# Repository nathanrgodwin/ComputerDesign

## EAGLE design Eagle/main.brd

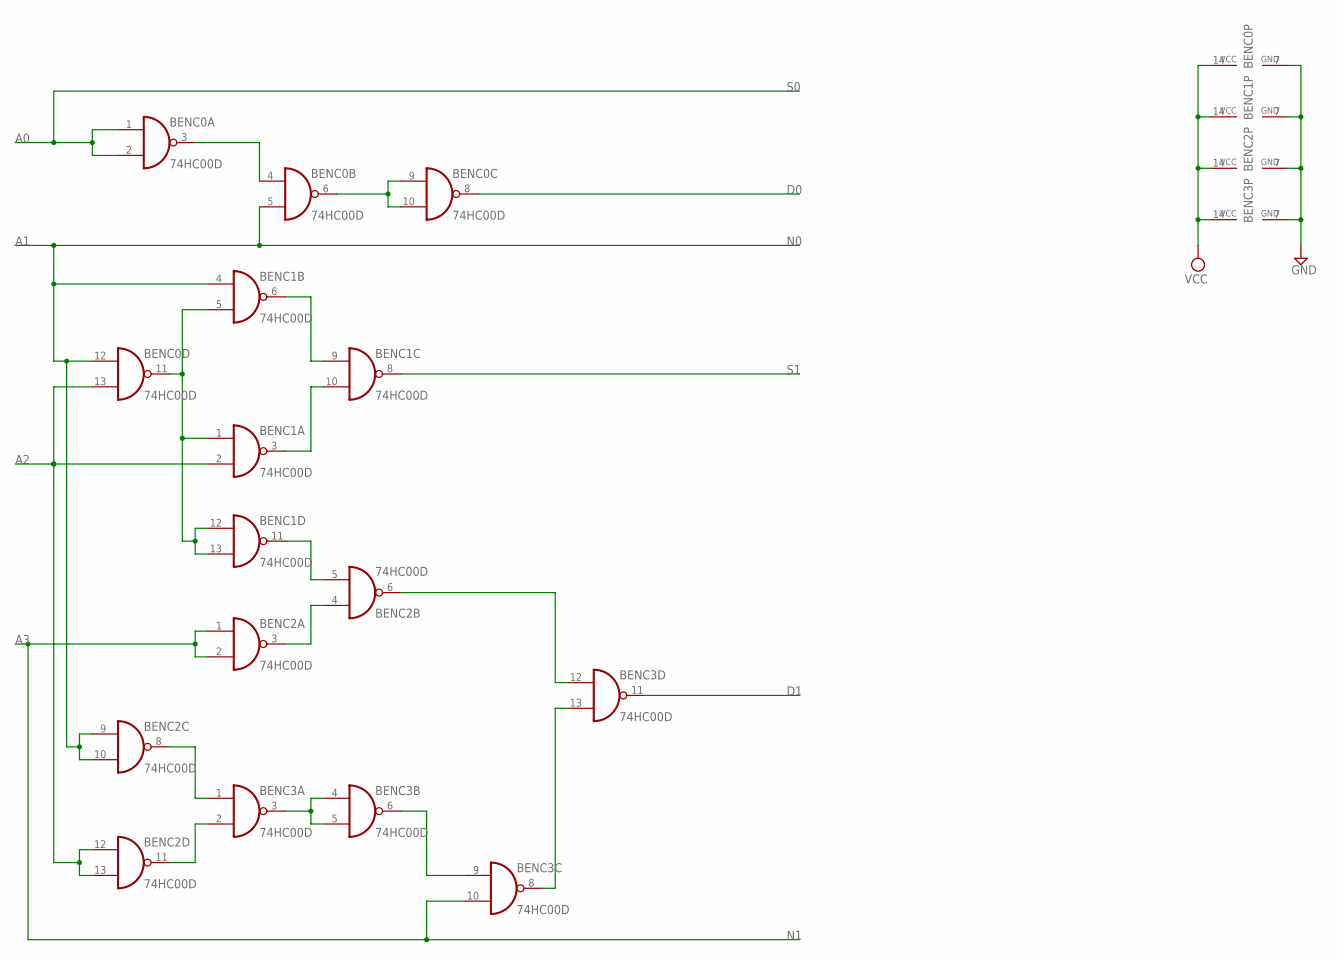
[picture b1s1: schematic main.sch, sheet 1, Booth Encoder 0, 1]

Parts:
BENC0, BENC1, BENC2, BENC3: 74HC00D; SO14

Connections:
A0: BENC0.1 (I0), BENC0.2 (I1); also elsewhere on the board
A1: BENC0.5 (I1), BENC0.12 (I0), BENC1.4 (I0), BENC2.9 (I0), BENC2.10 (I1); also elsewhere on the board
A2: BENC0.13 (I1), BENC1.2 (I1), BENC2.12 (I0), BENC2.13 (I1); also elsewhere on the board
A3: BENC2.1 (I0), BENC2.2 (I1), BENC3.10 (I1); also elsewhere on the board
D0: BENC0.8 (O); also elsewhere on the board
D1: BENC3.11 (O); also elsewhere on the board
GND: BENC0.7 (GND), BENC1.7 (GND), BENC2.7 (GND), BENC3.7 (GND); also elsewhere on the board
unnamed: BENC0.3 (O), BENC0.4 (I0)
unnamed: BENC0.6 (O), BENC0.9 (I0), BENC0.10 (I1)
unnamed: BENC2.6 (O), BENC3.12 (I0)
unnamed: BENC1.3 (O), BENC1.10 (I1)
unnamed: BENC1.6 (O), BENC1.9 (I0)
unnamed: BENC3.8 (O), BENC3.13 (I1)
unnamed: BENC2.3 (O), BENC2.4 (I0)
unnamed: BENC1.11 (O), BENC2.5 (I1)
unnamed: BENC2.11 (O), BENC3.2 (I1)
unnamed: BENC2.8 (O), BENC3.1 (I0)
unnamed: BENC3.3 (O), BENC3.4 (I0), BENC3.5 (I1)
unnamed: BENC3.6 (O), BENC3.9 (I0)
unnamed: BENC0.11 (O), BENC1.1 (I0), BENC1.5 (I1), BENC1.12 (I0), BENC1.13 (I1)
S1: BENC1.8 (O); also elsewhere on the board
VCC: BENC0.14 (VCC), BENC1.14 (VCC), BENC2.14 (VCC), BENC3.14 (VCC); also elsewhere on the board

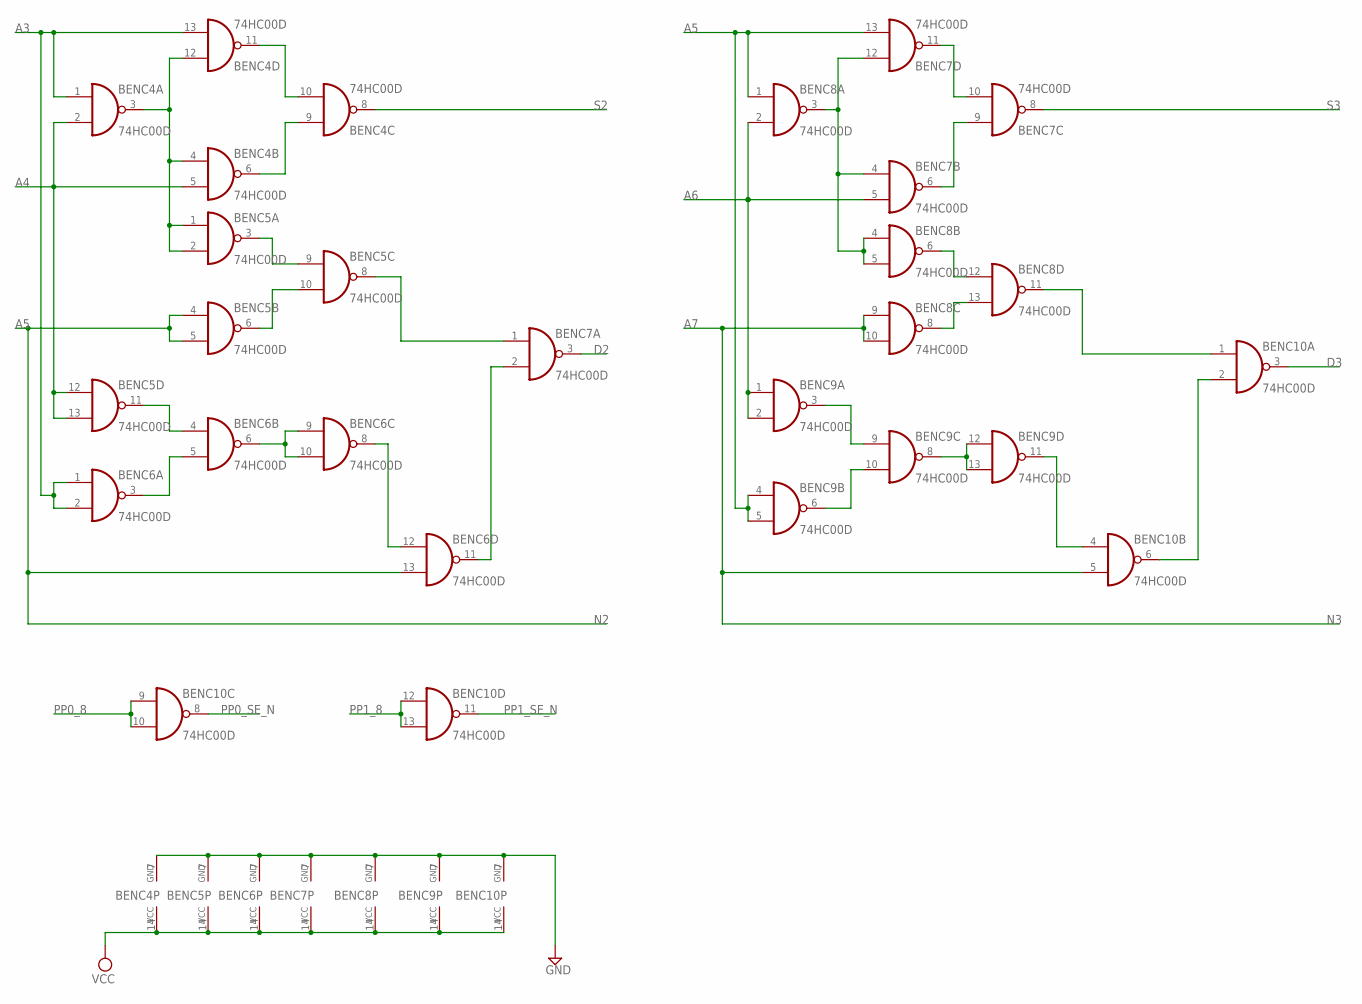
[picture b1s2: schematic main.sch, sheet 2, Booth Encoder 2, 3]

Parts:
BENC4, BENC5, BENC6, BENC7, BENC8, BENC9, BENC10: 74HC00D; SO14

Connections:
A3: BENC4.1 (I0), BENC4.13 (I1), BENC6.1 (I0), BENC6.2 (I1); also elsewhere on the board
A4: BENC4.2 (I1), BENC4.5 (I1), BENC5.12 (I0), BENC5.13 (I1); also elsewhere on the board
A5: BENC5.4 (I0), BENC5.5 (I1), BENC6.13 (I1), BENC7.13 (I1), BENC8.1 (I0), BENC9.4 (I0), BENC9.5 (I1); also elsewhere on the board
A6: BENC7.5 (I1), BENC8.2 (I1), BENC9.1 (I0), BENC9.2 (I1); also elsewhere on the board
A7: BENC8.9 (I0), BENC8.10 (I1), BENC10.5 (I1); also elsewhere on the board
D2: BENC7.3 (O); also elsewhere on the board
D3: BENC10.3 (O); also elsewhere on the board
GND: BENC4.7 (GND), BENC5.7 (GND), BENC6.7 (GND), BENC7.7 (GND), BENC8.7 (GND), BENC9.7 (GND), BENC10.7 (GND); also elsewhere on the board
unnamed: BENC4.3 (O), BENC4.4 (I0), BENC4.12 (I0), BENC5.1 (I0), BENC5.2 (I1)
unnamed: BENC4.6 (O), BENC4.9 (I0)
unnamed: BENC4.10 (I1), BENC4.11 (O)
unnamed: BENC6.11 (O), BENC7.2 (I1)
unnamed: BENC5.3 (O), BENC5.9 (I0)
unnamed: BENC5.6 (O), BENC5.10 (I1)
unnamed: BENC5.8 (O), BENC7.1 (I0)
unnamed: BENC6.6 (O), BENC6.9 (I0), BENC6.10 (I1)
unnamed: BENC6.8 (O), BENC6.12 (I0)
unnamed: BENC5.11 (O), BENC6.4 (I0)
unnamed: BENC6.3 (O), BENC6.5 (I1)
unnamed: BENC7.10 (I1), BENC7.11 (O)
unnamed: BENC7.6 (O), BENC7.9 (I0)
unnamed: BENC7.4 (I0), BENC7.12 (I0), BENC8.3 (O), BENC8.4 (I0), BENC8.5 (I1)
unnamed: BENC8.8 (O), BENC8.13 (I1)
unnamed: BENC8.6 (O), BENC8.12 (I0)
unnamed: BENC8.11 (O), BENC10.1 (I0)
unnamed: BENC10.2 (I1), BENC10.6 (O)
unnamed: BENC9.11 (O), BENC10.4 (I0)
unnamed: BENC9.8 (O), BENC9.12 (I0), BENC9.13 (I1)
unnamed: BENC9.6 (O), BENC9.10 (I1)
unnamed: BENC9.3 (O), BENC9.9 (I0)
PP0_8: BENC10.9 (I0), BENC10.10 (I1); also elsewhere on the board
PP0_SE_N: BENC10.8 (O); also elsewhere on the board
PP1_8: BENC10.12 (I0), BENC10.13 (I1); also elsewhere on the board
PP1_SE_N: BENC10.11 (O); also elsewhere on the board
S2: BENC4.8 (O); also elsewhere on the board
S3: BENC7.8 (O); also elsewhere on the board
VCC: BENC4.14 (VCC), BENC5.14 (VCC), BENC6.14 (VCC), BENC7.14 (VCC), BENC8.14 (VCC), BENC9.14 (VCC), BENC10.14 (VCC); also elsewhere on the board

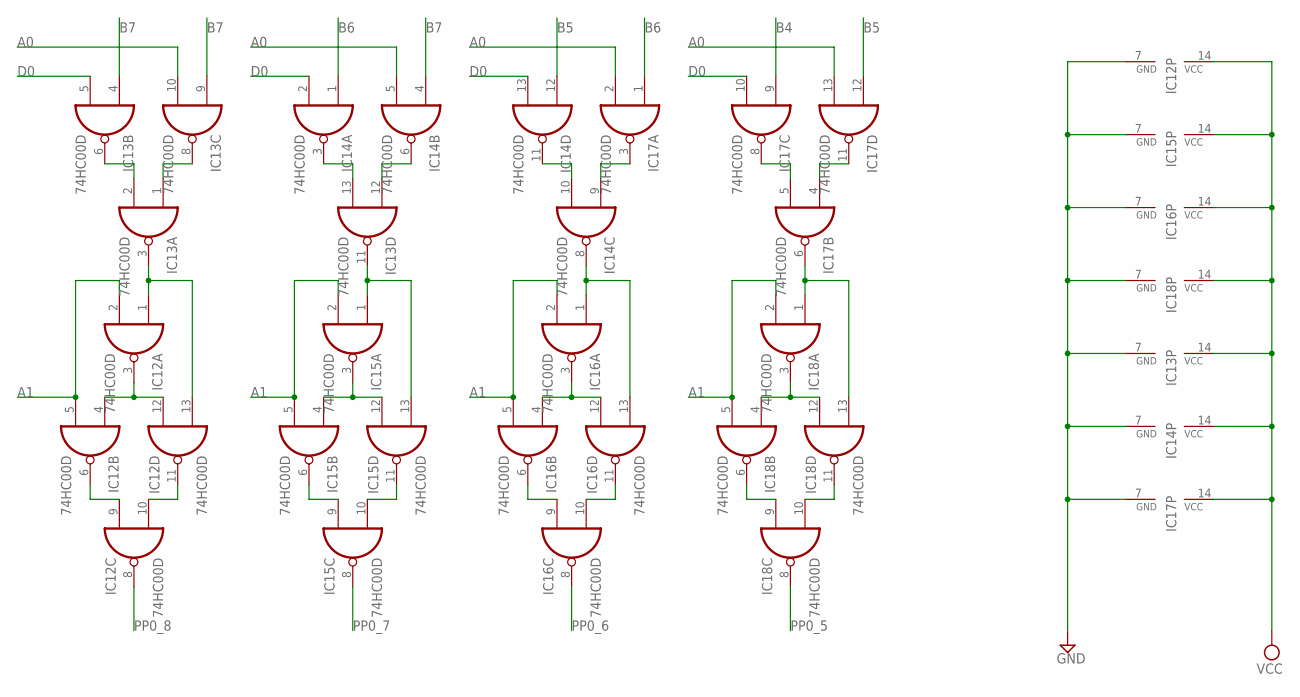
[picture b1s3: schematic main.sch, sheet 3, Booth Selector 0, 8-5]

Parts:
IC12, IC13, IC14, IC15, IC16, IC17, IC18: 74HC00D; SO14

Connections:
A0: IC13.10 (I1), IC14.5 (I1), IC17.2 (I1), IC17.13 (I1); also elsewhere on the board
A1: IC12.2 (I1), IC12.5 (I1), IC15.2 (I1), IC15.5 (I1), IC16.2 (I1), IC16.5 (I1), IC18.2 (I1), IC18.5 (I1); also elsewhere on the board
B4: IC17.9 (I0); also elsewhere on the board
B5: IC14.12 (I0), IC17.12 (I0); also elsewhere on the board
B6: IC14.1 (I0), IC17.1 (I0); also elsewhere on the board
B7: IC13.4 (I0), IC13.9 (I0), IC14.4 (I0); also elsewhere on the board
D0: IC13.5 (I1), IC14.2 (I1), IC14.13 (I1), IC17.10 (I1); also elsewhere on the board
GND: IC12.7 (GND), IC13.7 (GND), IC14.7 (GND), IC15.7 (GND), IC16.7 (GND), IC17.7 (GND), IC18.7 (GND); also elsewhere on the board
unnamed: IC12.6 (O), IC12.9 (I0)
unnamed: IC12.10 (I1), IC12.11 (O)
unnamed: IC12.3 (O), IC12.4 (I0), IC12.12 (I0)
unnamed: IC15.6 (O), IC15.9 (I0)
unnamed: IC15.10 (I1), IC15.11 (O)
unnamed: IC15.3 (O), IC15.4 (I0), IC15.12 (I0)
unnamed: IC16.3 (O), IC16.4 (I0), IC16.12 (I0)
unnamed: IC16.10 (I1), IC16.11 (O)
unnamed: IC16.6 (O), IC16.9 (I0)
unnamed: IC13.11 (O), IC15.1 (I0), IC15.13 (I1)
unnamed: IC13.13 (I1), IC14.3 (O)
unnamed: IC13.12 (I0), IC14.6 (O)
unnamed: IC13.1 (I0), IC13.8 (O)
unnamed: IC13.2 (I1), IC13.6 (O)
unnamed: IC14.10 (I1), IC14.11 (O)
unnamed: IC14.9 (I0), IC17.3 (O)
unnamed: IC17.5 (I1), IC17.8 (O)
unnamed: IC17.4 (I0), IC17.11 (O)
unnamed: IC17.6 (O), IC18.1 (I0), IC18.13 (I1)
unnamed: IC14.8 (O), IC16.1 (I0), IC16.13 (I1)
unnamed: IC12.1 (I0), IC12.13 (I1), IC13.3 (O)
unnamed: IC18.3 (O), IC18.4 (I0), IC18.12 (I0)
unnamed: IC18.6 (O), IC18.9 (I0)
unnamed: IC18.10 (I1), IC18.11 (O)
PP0_5: IC18.8 (O); also elsewhere on the board
PP0_6: IC16.8 (O); also elsewhere on the board
PP0_7: IC15.8 (O); also elsewhere on the board
PP0_8: IC12.8 (O); also elsewhere on the board
VCC: IC12.14 (VCC), IC13.14 (VCC), IC14.14 (VCC), IC15.14 (VCC), IC16.14 (VCC), IC17.14 (VCC), IC18.14 (VCC); also elsewhere on the board

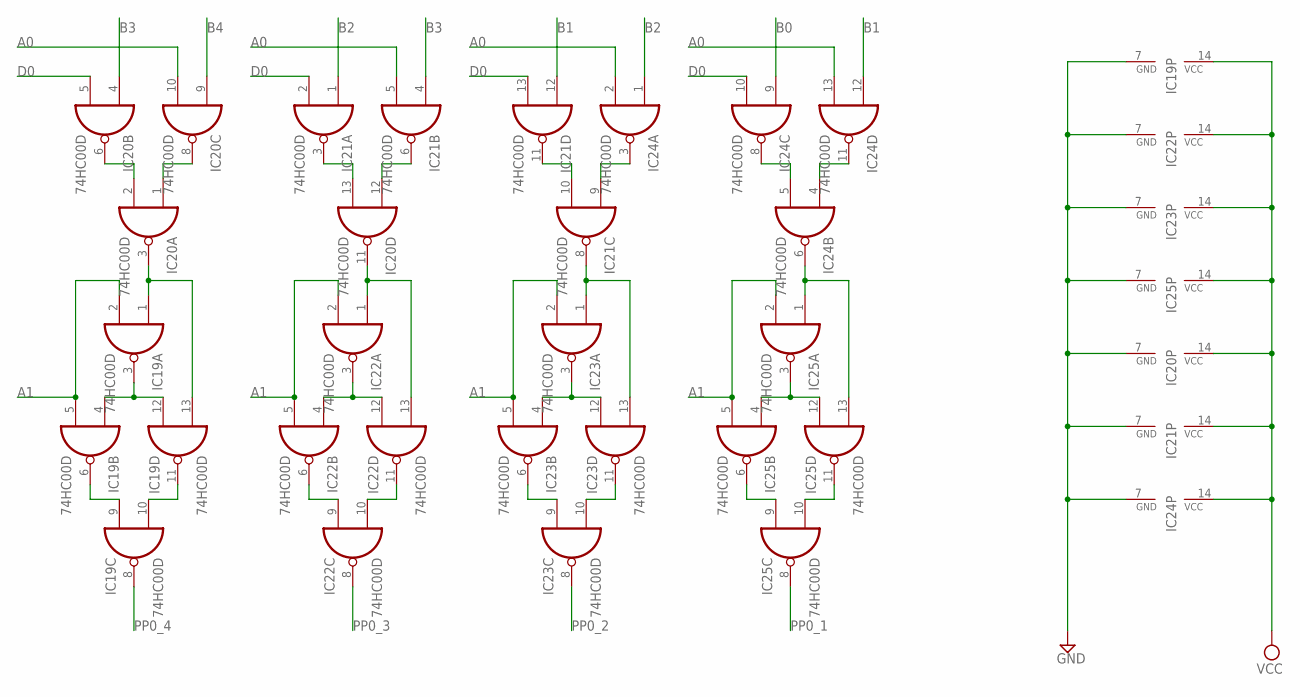
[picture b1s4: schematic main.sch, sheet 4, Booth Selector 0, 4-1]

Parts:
IC19, IC20, IC21, IC22, IC23, IC24, IC25: 74HC00D; SO14

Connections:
A0: IC20.10 (I1), IC21.5 (I1), IC24.2 (I1), IC24.13 (I1); also elsewhere on the board
A1: IC19.2 (I1), IC19.5 (I1), IC22.2 (I1), IC22.5 (I1), IC23.2 (I1), IC23.5 (I1), IC25.2 (I1), IC25.5 (I1); also elsewhere on the board
B0: IC24.9 (I0); also elsewhere on the board
B1: IC21.12 (I0), IC24.12 (I0); also elsewhere on the board
B2: IC21.1 (I0), IC24.1 (I0); also elsewhere on the board
B3: IC20.4 (I0), IC21.4 (I0); also elsewhere on the board
B4: IC20.9 (I0); also elsewhere on the board
D0: IC20.5 (I1), IC21.2 (I1), IC21.13 (I1), IC24.10 (I1); also elsewhere on the board
GND: IC19.7 (GND), IC20.7 (GND), IC21.7 (GND), IC22.7 (GND), IC23.7 (GND), IC24.7 (GND), IC25.7 (GND); also elsewhere on the board
unnamed: IC19.6 (O), IC19.9 (I0)
unnamed: IC19.10 (I1), IC19.11 (O)
unnamed: IC19.3 (O), IC19.4 (I0), IC19.12 (I0)
unnamed: IC22.6 (O), IC22.9 (I0)
unnamed: IC22.10 (I1), IC22.11 (O)
unnamed: IC22.3 (O), IC22.4 (I0), IC22.12 (I0)
unnamed: IC23.3 (O), IC23.4 (I0), IC23.12 (I0)
unnamed: IC23.10 (I1), IC23.11 (O)
unnamed: IC23.6 (O), IC23.9 (I0)
unnamed: IC20.11 (O), IC22.1 (I0), IC22.13 (I1)
unnamed: IC20.13 (I1), IC21.3 (O)
unnamed: IC20.12 (I0), IC21.6 (O)
unnamed: IC20.1 (I0), IC20.8 (O)
unnamed: IC20.2 (I1), IC20.6 (O)
unnamed: IC21.10 (I1), IC21.11 (O)
unnamed: IC21.9 (I0), IC24.3 (O)
unnamed: IC24.5 (I1), IC24.8 (O)
unnamed: IC24.4 (I0), IC24.11 (O)
unnamed: IC24.6 (O), IC25.1 (I0), IC25.13 (I1)
unnamed: IC21.8 (O), IC23.1 (I0), IC23.13 (I1)
unnamed: IC19.1 (I0), IC19.13 (I1), IC20.3 (O)
unnamed: IC25.3 (O), IC25.4 (I0), IC25.12 (I0)
unnamed: IC25.6 (O), IC25.9 (I0)
unnamed: IC25.10 (I1), IC25.11 (O)
PP0_1: IC25.8 (O); also elsewhere on the board
PP0_2: IC23.8 (O); also elsewhere on the board
PP0_3: IC22.8 (O); also elsewhere on the board
PP0_4: IC19.8 (O); also elsewhere on the board
VCC: IC19.14 (VCC), IC20.14 (VCC), IC21.14 (VCC), IC22.14 (VCC), IC23.14 (VCC), IC24.14 (VCC), IC25.14 (VCC); also elsewhere on the board

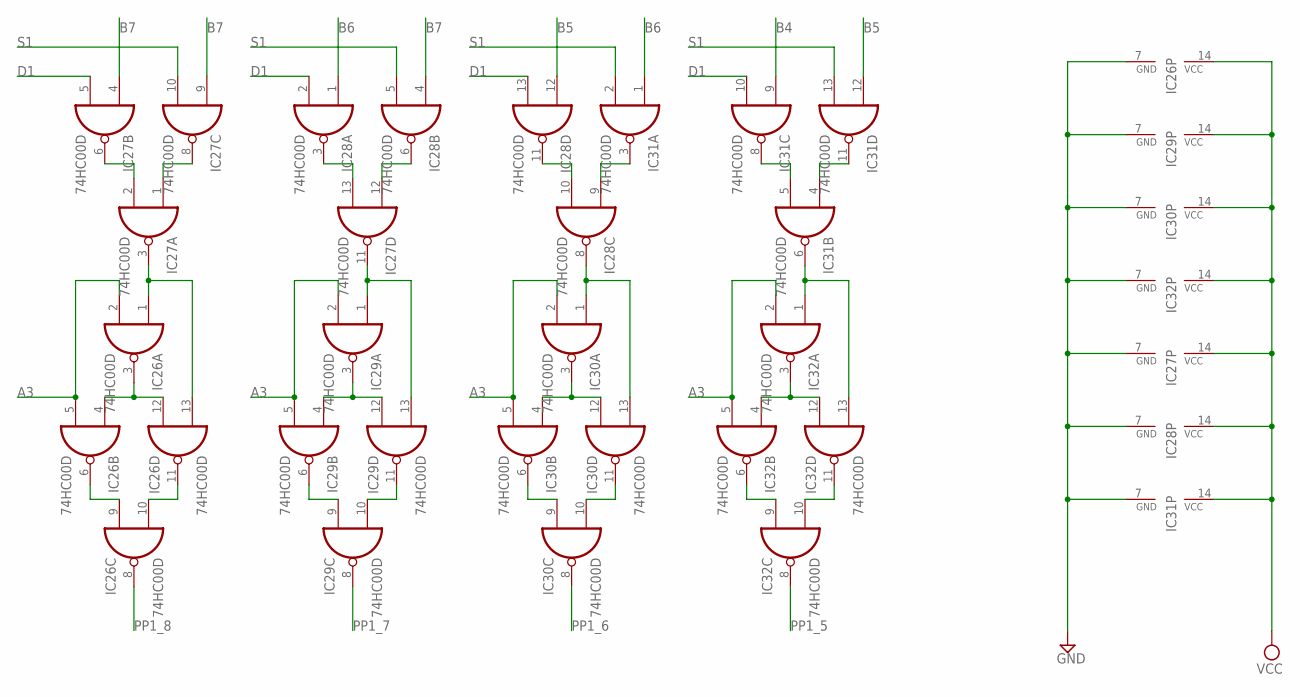
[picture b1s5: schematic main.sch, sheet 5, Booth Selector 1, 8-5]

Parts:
IC26, IC27, IC28, IC29, IC30, IC31, IC32: 74HC00D; SO14

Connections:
A3: IC26.2 (I1), IC26.5 (I1), IC29.2 (I1), IC29.5 (I1), IC30.2 (I1), IC30.5 (I1), IC32.2 (I1), IC32.5 (I1); also elsewhere on the board
B4: IC31.9 (I0); also elsewhere on the board
B5: IC28.12 (I0), IC31.12 (I0); also elsewhere on the board
B6: IC28.1 (I0), IC31.1 (I0); also elsewhere on the board
B7: IC27.4 (I0), IC27.9 (I0), IC28.4 (I0); also elsewhere on the board
D1: IC27.5 (I1), IC28.2 (I1), IC28.13 (I1), IC31.10 (I1); also elsewhere on the board
GND: IC26.7 (GND), IC27.7 (GND), IC28.7 (GND), IC29.7 (GND), IC30.7 (GND), IC31.7 (GND), IC32.7 (GND); also elsewhere on the board
unnamed: IC26.6 (O), IC26.9 (I0)
unnamed: IC26.10 (I1), IC26.11 (O)
unnamed: IC26.3 (O), IC26.4 (I0), IC26.12 (I0)
unnamed: IC29.6 (O), IC29.9 (I0)
unnamed: IC29.10 (I1), IC29.11 (O)
unnamed: IC29.3 (O), IC29.4 (I0), IC29.12 (I0)
unnamed: IC30.3 (O), IC30.4 (I0), IC30.12 (I0)
unnamed: IC30.10 (I1), IC30.11 (O)
unnamed: IC30.6 (O), IC30.9 (I0)
unnamed: IC27.11 (O), IC29.1 (I0), IC29.13 (I1)
unnamed: IC27.13 (I1), IC28.3 (O)
unnamed: IC27.12 (I0), IC28.6 (O)
unnamed: IC27.1 (I0), IC27.8 (O)
unnamed: IC27.2 (I1), IC27.6 (O)
unnamed: IC28.10 (I1), IC28.11 (O)
unnamed: IC28.9 (I0), IC31.3 (O)
unnamed: IC31.5 (I1), IC31.8 (O)
unnamed: IC31.4 (I0), IC31.11 (O)
unnamed: IC31.6 (O), IC32.1 (I0), IC32.13 (I1)
unnamed: IC28.8 (O), IC30.1 (I0), IC30.13 (I1)
unnamed: IC26.1 (I0), IC26.13 (I1), IC27.3 (O)
unnamed: IC32.3 (O), IC32.4 (I0), IC32.12 (I0)
unnamed: IC32.6 (O), IC32.9 (I0)
unnamed: IC32.10 (I1), IC32.11 (O)
PP1_5: IC32.8 (O); also elsewhere on the board
PP1_6: IC30.8 (O); also elsewhere on the board
PP1_7: IC29.8 (O); also elsewhere on the board
PP1_8: IC26.8 (O); also elsewhere on the board
S1: IC27.10 (I1), IC28.5 (I1), IC31.2 (I1), IC31.13 (I1); also elsewhere on the board
VCC: IC26.14 (VCC), IC27.14 (VCC), IC28.14 (VCC), IC29.14 (VCC), IC30.14 (VCC), IC31.14 (VCC), IC32.14 (VCC); also elsewhere on the board

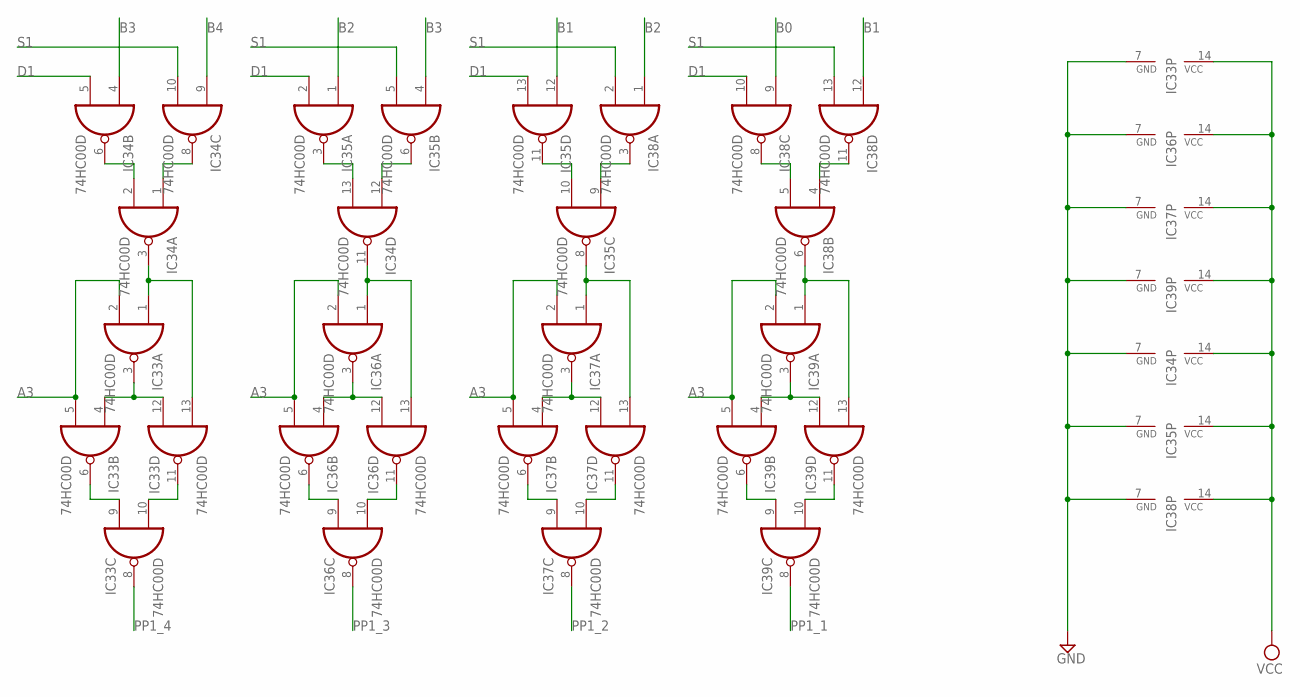
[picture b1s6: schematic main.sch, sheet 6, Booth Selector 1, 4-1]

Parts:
IC33, IC34, IC35, IC36, IC37, IC38, IC39: 74HC00D; SO14

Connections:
A3: IC33.2 (I1), IC33.5 (I1), IC36.2 (I1), IC36.5 (I1), IC37.2 (I1), IC37.5 (I1), IC39.2 (I1), IC39.5 (I1); also elsewhere on the board
B0: IC38.9 (I0); also elsewhere on the board
B1: IC35.12 (I0), IC38.12 (I0); also elsewhere on the board
B2: IC35.1 (I0), IC38.1 (I0); also elsewhere on the board
B3: IC34.4 (I0), IC35.4 (I0); also elsewhere on the board
B4: IC34.9 (I0); also elsewhere on the board
D1: IC34.5 (I1), IC35.2 (I1), IC35.13 (I1), IC38.10 (I1); also elsewhere on the board
GND: IC33.7 (GND), IC34.7 (GND), IC35.7 (GND), IC36.7 (GND), IC37.7 (GND), IC38.7 (GND), IC39.7 (GND); also elsewhere on the board
unnamed: IC33.6 (O), IC33.9 (I0)
unnamed: IC33.10 (I1), IC33.11 (O)
unnamed: IC33.3 (O), IC33.4 (I0), IC33.12 (I0)
unnamed: IC36.6 (O), IC36.9 (I0)
unnamed: IC36.10 (I1), IC36.11 (O)
unnamed: IC36.3 (O), IC36.4 (I0), IC36.12 (I0)
unnamed: IC37.3 (O), IC37.4 (I0), IC37.12 (I0)
unnamed: IC37.10 (I1), IC37.11 (O)
unnamed: IC37.6 (O), IC37.9 (I0)
unnamed: IC34.11 (O), IC36.1 (I0), IC36.13 (I1)
unnamed: IC34.13 (I1), IC35.3 (O)
unnamed: IC34.12 (I0), IC35.6 (O)
unnamed: IC34.1 (I0), IC34.8 (O)
unnamed: IC34.2 (I1), IC34.6 (O)
unnamed: IC35.10 (I1), IC35.11 (O)
unnamed: IC35.9 (I0), IC38.3 (O)
unnamed: IC38.5 (I1), IC38.8 (O)
unnamed: IC38.4 (I0), IC38.11 (O)
unnamed: IC38.6 (O), IC39.1 (I0), IC39.13 (I1)
unnamed: IC35.8 (O), IC37.1 (I0), IC37.13 (I1)
unnamed: IC33.1 (I0), IC33.13 (I1), IC34.3 (O)
unnamed: IC39.3 (O), IC39.4 (I0), IC39.12 (I0)
unnamed: IC39.6 (O), IC39.9 (I0)
unnamed: IC39.10 (I1), IC39.11 (O)
PP1_1: IC39.8 (O); also elsewhere on the board
PP1_2: IC37.8 (O); also elsewhere on the board
PP1_3: IC36.8 (O); also elsewhere on the board
PP1_4: IC33.8 (O); also elsewhere on the board
S1: IC34.10 (I1), IC35.5 (I1), IC38.2 (I1), IC38.13 (I1); also elsewhere on the board
VCC: IC33.14 (VCC), IC34.14 (VCC), IC35.14 (VCC), IC36.14 (VCC), IC37.14 (VCC), IC38.14 (VCC), IC39.14 (VCC); also elsewhere on the board

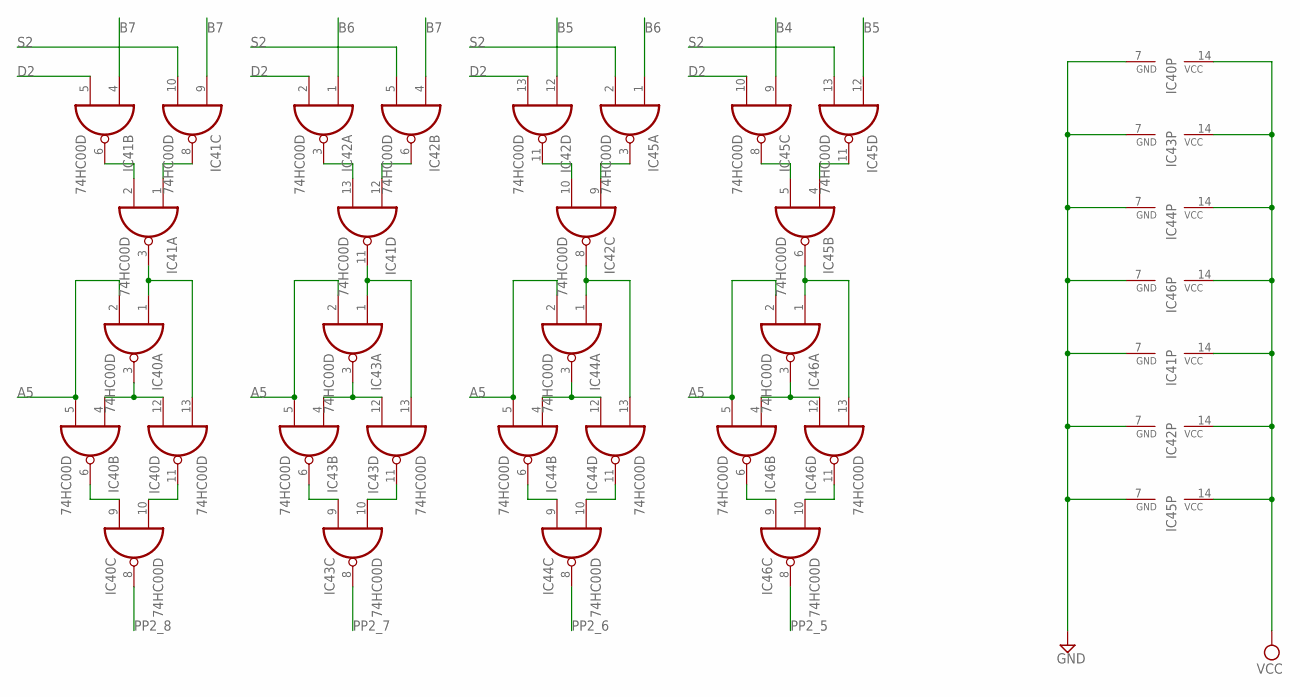
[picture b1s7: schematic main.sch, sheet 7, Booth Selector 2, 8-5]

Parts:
IC40, IC41, IC42, IC43, IC44, IC45, IC46: 74HC00D; SO14

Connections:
A5: IC40.2 (I1), IC40.5 (I1), IC43.2 (I1), IC43.5 (I1), IC44.2 (I1), IC44.5 (I1), IC46.2 (I1), IC46.5 (I1); also elsewhere on the board
B4: IC45.9 (I0); also elsewhere on the board
B5: IC42.12 (I0), IC45.12 (I0); also elsewhere on the board
B6: IC42.1 (I0), IC45.1 (I0); also elsewhere on the board
B7: IC41.4 (I0), IC41.9 (I0), IC42.4 (I0); also elsewhere on the board
D2: IC41.5 (I1), IC42.2 (I1), IC42.13 (I1), IC45.10 (I1); also elsewhere on the board
GND: IC40.7 (GND), IC41.7 (GND), IC42.7 (GND), IC43.7 (GND), IC44.7 (GND), IC45.7 (GND), IC46.7 (GND); also elsewhere on the board
unnamed: IC40.6 (O), IC40.9 (I0)
unnamed: IC40.10 (I1), IC40.11 (O)
unnamed: IC40.3 (O), IC40.4 (I0), IC40.12 (I0)
unnamed: IC43.6 (O), IC43.9 (I0)
unnamed: IC43.10 (I1), IC43.11 (O)
unnamed: IC43.3 (O), IC43.4 (I0), IC43.12 (I0)
unnamed: IC44.3 (O), IC44.4 (I0), IC44.12 (I0)
unnamed: IC44.10 (I1), IC44.11 (O)
unnamed: IC44.6 (O), IC44.9 (I0)
unnamed: IC41.11 (O), IC43.1 (I0), IC43.13 (I1)
unnamed: IC41.13 (I1), IC42.3 (O)
unnamed: IC41.12 (I0), IC42.6 (O)
unnamed: IC41.1 (I0), IC41.8 (O)
unnamed: IC41.2 (I1), IC41.6 (O)
unnamed: IC42.10 (I1), IC42.11 (O)
unnamed: IC42.9 (I0), IC45.3 (O)
unnamed: IC45.5 (I1), IC45.8 (O)
unnamed: IC45.4 (I0), IC45.11 (O)
unnamed: IC45.6 (O), IC46.1 (I0), IC46.13 (I1)
unnamed: IC42.8 (O), IC44.1 (I0), IC44.13 (I1)
unnamed: IC40.1 (I0), IC40.13 (I1), IC41.3 (O)
unnamed: IC46.3 (O), IC46.4 (I0), IC46.12 (I0)
unnamed: IC46.6 (O), IC46.9 (I0)
unnamed: IC46.10 (I1), IC46.11 (O)
PP2_5: IC46.8 (O); also elsewhere on the board
PP2_6: IC44.8 (O); also elsewhere on the board
PP2_7: IC43.8 (O); also elsewhere on the board
PP2_8: IC40.8 (O); also elsewhere on the board
S2: IC41.10 (I1), IC42.5 (I1), IC45.2 (I1), IC45.13 (I1); also elsewhere on the board
VCC: IC40.14 (VCC), IC41.14 (VCC), IC42.14 (VCC), IC43.14 (VCC), IC44.14 (VCC), IC45.14 (VCC), IC46.14 (VCC); also elsewhere on the board

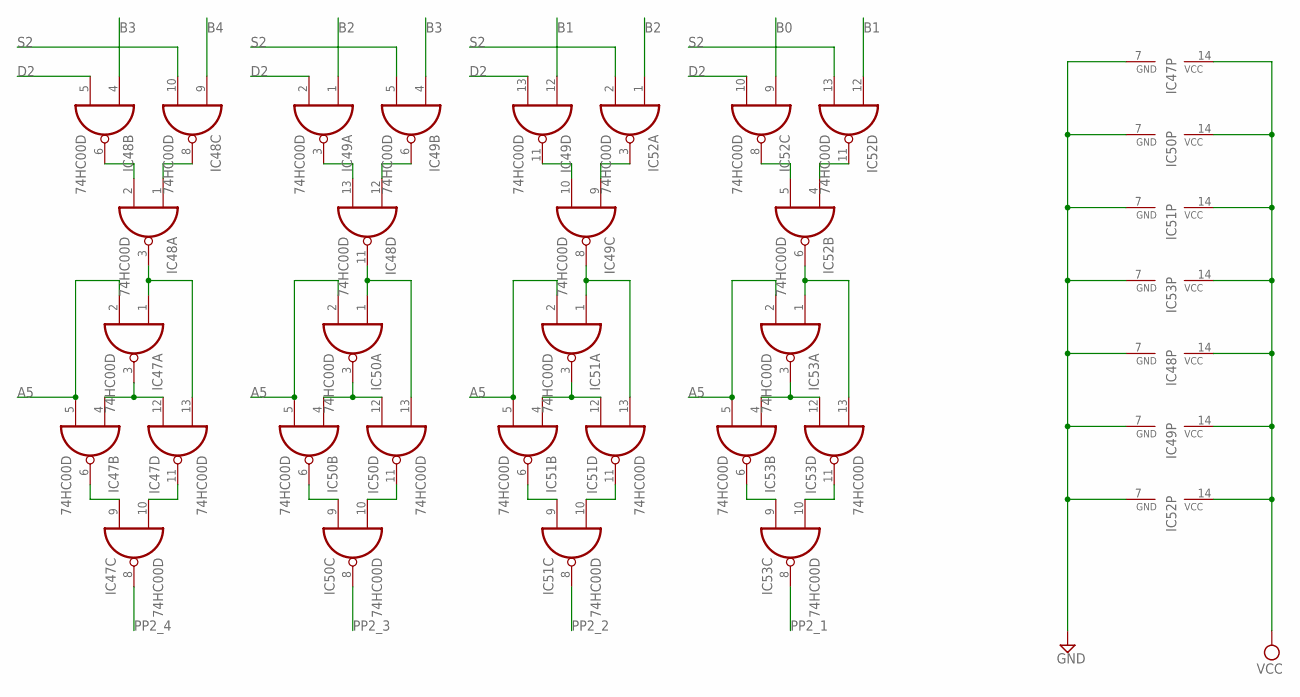
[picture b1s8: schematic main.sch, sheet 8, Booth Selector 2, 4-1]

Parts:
IC47, IC48, IC49, IC50, IC51, IC52, IC53: 74HC00D; SO14

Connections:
A5: IC47.2 (I1), IC47.5 (I1), IC50.2 (I1), IC50.5 (I1), IC51.2 (I1), IC51.5 (I1), IC53.2 (I1), IC53.5 (I1); also elsewhere on the board
B0: IC52.9 (I0); also elsewhere on the board
B1: IC49.12 (I0), IC52.12 (I0); also elsewhere on the board
B2: IC49.1 (I0), IC52.1 (I0); also elsewhere on the board
B3: IC48.4 (I0), IC49.4 (I0); also elsewhere on the board
B4: IC48.9 (I0); also elsewhere on the board
D2: IC48.5 (I1), IC49.2 (I1), IC49.13 (I1), IC52.10 (I1); also elsewhere on the board
GND: IC47.7 (GND), IC48.7 (GND), IC49.7 (GND), IC50.7 (GND), IC51.7 (GND), IC52.7 (GND), IC53.7 (GND); also elsewhere on the board
unnamed: IC47.6 (O), IC47.9 (I0)
unnamed: IC47.10 (I1), IC47.11 (O)
unnamed: IC47.3 (O), IC47.4 (I0), IC47.12 (I0)
unnamed: IC50.6 (O), IC50.9 (I0)
unnamed: IC50.10 (I1), IC50.11 (O)
unnamed: IC50.3 (O), IC50.4 (I0), IC50.12 (I0)
unnamed: IC51.3 (O), IC51.4 (I0), IC51.12 (I0)
unnamed: IC51.10 (I1), IC51.11 (O)
unnamed: IC51.6 (O), IC51.9 (I0)
unnamed: IC48.11 (O), IC50.1 (I0), IC50.13 (I1)
unnamed: IC48.13 (I1), IC49.3 (O)
unnamed: IC48.12 (I0), IC49.6 (O)
unnamed: IC48.1 (I0), IC48.8 (O)
unnamed: IC48.2 (I1), IC48.6 (O)
unnamed: IC49.10 (I1), IC49.11 (O)
unnamed: IC49.9 (I0), IC52.3 (O)
unnamed: IC52.5 (I1), IC52.8 (O)
unnamed: IC52.4 (I0), IC52.11 (O)
unnamed: IC52.6 (O), IC53.1 (I0), IC53.13 (I1)
unnamed: IC49.8 (O), IC51.1 (I0), IC51.13 (I1)
unnamed: IC47.1 (I0), IC47.13 (I1), IC48.3 (O)
unnamed: IC53.3 (O), IC53.4 (I0), IC53.12 (I0)
unnamed: IC53.6 (O), IC53.9 (I0)
unnamed: IC53.10 (I1), IC53.11 (O)
PP2_1: IC53.8 (O); also elsewhere on the board
PP2_2: IC51.8 (O); also elsewhere on the board
PP2_3: IC50.8 (O); also elsewhere on the board
PP2_4: IC47.8 (O); also elsewhere on the board
S2: IC48.10 (I1), IC49.5 (I1), IC52.2 (I1), IC52.13 (I1); also elsewhere on the board
VCC: IC47.14 (VCC), IC48.14 (VCC), IC49.14 (VCC), IC50.14 (VCC), IC51.14 (VCC), IC52.14 (VCC), IC53.14 (VCC); also elsewhere on the board

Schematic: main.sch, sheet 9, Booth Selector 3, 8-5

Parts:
IC54, IC55, IC56, IC57, IC58, IC59, IC60: 74HC00D; SO14

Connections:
A7: IC54.2 (I1), IC54.5 (I1), IC57.2 (I1), IC57.5 (I1), IC58.2 (I1), IC58.5 (I1), IC60.2 (I1), IC60.5 (I1); also elsewhere on the board
B4: IC59.9 (I0); also elsewhere on the board
B5: IC56.12 (I0), IC59.12 (I0); also elsewhere on the board
B6: IC56.1 (I0), IC59.1 (I0); also elsewhere on the board
B7: IC55.4 (I0), IC55.9 (I0), IC56.4 (I0); also elsewhere on the board
D3: IC55.5 (I1), IC56.2 (I1), IC56.13 (I1), IC59.10 (I1); also elsewhere on the board
GND: IC54.7 (GND), IC55.7 (GND), IC56.7 (GND), IC57.7 (GND), IC58.7 (GND), IC59.7 (GND), IC60.7 (GND); also elsewhere on the board
unnamed: IC54.6 (O), IC54.9 (I0)
unnamed: IC54.10 (I1), IC54.11 (O)
unnamed: IC54.3 (O), IC54.4 (I0), IC54.12 (I0)
unnamed: IC57.6 (O), IC57.9 (I0)
unnamed: IC57.10 (I1), IC57.11 (O)
unnamed: IC57.3 (O), IC57.4 (I0), IC57.12 (I0)
unnamed: IC58.3 (O), IC58.4 (I0), IC58.12 (I0)
unnamed: IC58.10 (I1), IC58.11 (O)
unnamed: IC58.6 (O), IC58.9 (I0)
unnamed: IC55.11 (O), IC57.1 (I0), IC57.13 (I1)
unnamed: IC55.13 (I1), IC56.3 (O)
unnamed: IC55.12 (I0), IC56.6 (O)
unnamed: IC55.1 (I0), IC55.8 (O)
unnamed: IC55.2 (I1), IC55.6 (O)
unnamed: IC56.10 (I1), IC56.11 (O)
unnamed: IC56.9 (I0), IC59.3 (O)
unnamed: IC59.5 (I1), IC59.8 (O)
unnamed: IC59.4 (I0), IC59.11 (O)
unnamed: IC59.6 (O), IC60.1 (I0), IC60.13 (I1)
unnamed: IC56.8 (O), IC58.1 (I0), IC58.13 (I1)
unnamed: IC54.1 (I0), IC54.13 (I1), IC55.3 (O)
unnamed: IC60.3 (O), IC60.4 (I0), IC60.12 (I0)
unnamed: IC60.6 (O), IC60.9 (I0)
unnamed: IC60.10 (I1), IC60.11 (O)
PP3_5: IC60.8 (O); also elsewhere on the board
PP3_6: IC58.8 (O); also elsewhere on the board
PP3_7: IC57.8 (O); also elsewhere on the board
PP3_8: IC54.8 (O); also elsewhere on the board
S3: IC55.10 (I1), IC56.5 (I1), IC59.2 (I1), IC59.13 (I1); also elsewhere on the board
VCC: IC54.14 (VCC), IC55.14 (VCC), IC56.14 (VCC), IC57.14 (VCC), IC58.14 (VCC), IC59.14 (VCC), IC60.14 (VCC); also elsewhere on the board

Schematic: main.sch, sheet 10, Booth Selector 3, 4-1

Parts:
IC61, IC62, IC63, IC64, IC65, IC66, IC67: 74HC00D; SO14

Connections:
A7: IC61.2 (I1), IC61.5 (I1), IC64.2 (I1), IC64.5 (I1), IC65.2 (I1), IC65.5 (I1), IC67.2 (I1), IC67.5 (I1); also elsewhere on the board
B0: IC66.9 (I0); also elsewhere on the board
B1: IC63.12 (I0), IC66.12 (I0); also elsewhere on the board
B2: IC63.1 (I0), IC66.1 (I0); also elsewhere on the board
B3: IC62.4 (I0), IC63.4 (I0); also elsewhere on the board
B4: IC62.9 (I0); also elsewhere on the board
D3: IC62.5 (I1), IC63.2 (I1), IC63.13 (I1), IC66.10 (I1); also elsewhere on the board
GND: IC61.7 (GND), IC62.7 (GND), IC63.7 (GND), IC64.7 (GND), IC65.7 (GND), IC66.7 (GND), IC67.7 (GND); also elsewhere on the board
unnamed: IC61.6 (O), IC61.9 (I0)
unnamed: IC61.10 (I1), IC61.11 (O)
unnamed: IC61.3 (O), IC61.4 (I0), IC61.12 (I0)
unnamed: IC64.6 (O), IC64.9 (I0)
unnamed: IC64.10 (I1), IC64.11 (O)
unnamed: IC64.3 (O), IC64.4 (I0), IC64.12 (I0)
unnamed: IC65.3 (O), IC65.4 (I0), IC65.12 (I0)
unnamed: IC65.10 (I1), IC65.11 (O)
unnamed: IC65.6 (O), IC65.9 (I0)
unnamed: IC62.11 (O), IC64.1 (I0), IC64.13 (I1)
unnamed: IC62.13 (I1), IC63.3 (O)
unnamed: IC62.12 (I0), IC63.6 (O)
unnamed: IC62.1 (I0), IC62.8 (O)
unnamed: IC62.2 (I1), IC62.6 (O)
unnamed: IC63.10 (I1), IC63.11 (O)
unnamed: IC63.9 (I0), IC66.3 (O)
unnamed: IC66.5 (I1), IC66.8 (O)
unnamed: IC66.4 (I0), IC66.11 (O)
unnamed: IC66.6 (O), IC67.1 (I0), IC67.13 (I1)
unnamed: IC63.8 (O), IC65.1 (I0), IC65.13 (I1)
unnamed: IC61.1 (I0), IC61.13 (I1), IC62.3 (O)
unnamed: IC67.3 (O), IC67.4 (I0), IC67.12 (I0)
unnamed: IC67.6 (O), IC67.9 (I0)
unnamed: IC67.10 (I1), IC67.11 (O)
PP3_1: IC67.8 (O); also elsewhere on the board
PP3_2: IC65.8 (O); also elsewhere on the board
PP3_3: IC64.8 (O); also elsewhere on the board
PP3_4: IC61.8 (O); also elsewhere on the board
S3: IC62.10 (I1), IC63.5 (I1), IC66.2 (I1), IC66.13 (I1); also elsewhere on the board
VCC: IC61.14 (VCC), IC62.14 (VCC), IC63.14 (VCC), IC64.14 (VCC), IC65.14 (VCC), IC66.14 (VCC), IC67.14 (VCC); also elsewhere on the board

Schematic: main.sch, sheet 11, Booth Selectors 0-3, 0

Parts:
IC68, IC69, IC70, IC71, IC72, IC73: 74HC00D; SO14

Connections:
A0: IC69.2 (I1); also elsewhere on the board
A1: IC68.2 (I1), IC68.5 (I1); also elsewhere on the board
A3: IC70.2 (I1), IC70.5 (I1); also elsewhere on the board
A5: IC71.2 (I1), IC71.5 (I1); also elsewhere on the board
A7: IC73.2 (I1), IC73.5 (I1); also elsewhere on the board
B0: IC69.1 (I0), IC69.12 (I0), IC72.4 (I0), IC72.9 (I0); also elsewhere on the board
GND: IC68.7 (GND), IC69.7 (GND), IC70.7 (GND), IC71.7 (GND), IC72.7 (GND), IC73.7 (GND); also elsewhere on the board
unnamed: IC68.6 (O), IC68.9 (I0)
unnamed: IC68.10 (I1), IC68.11 (O)
unnamed: IC68.3 (O), IC68.4 (I0), IC68.12 (I0)
unnamed: IC70.3 (O), IC70.4 (I0), IC70.12 (I0)
unnamed: IC70.10 (I1), IC70.11 (O)
unnamed: IC70.6 (O), IC70.9 (I0)
unnamed: IC69.8 (O), IC70.1 (I0), IC70.13 (I1)
unnamed: IC69.9 (I0), IC69.10 (I1), IC69.11 (O)
unnamed: IC72.1 (I0), IC72.2 (I1), IC72.6 (O)
unnamed: IC72.8 (O), IC72.12 (I0), IC72.13 (I1)
unnamed: IC73.3 (O), IC73.4 (I0), IC73.12 (I0)
unnamed: IC71.3 (O), IC71.4 (I0), IC71.12 (I0)
unnamed: IC71.6 (O), IC71.9 (I0)
unnamed: IC71.10 (I1), IC71.11 (O)
unnamed: IC73.6 (O), IC73.9 (I0)
unnamed: IC73.10 (I1), IC73.11 (O)
unnamed: IC71.1 (I0), IC71.13 (I1), IC72.3 (O)
unnamed: IC72.11 (O), IC73.1 (I0), IC73.13 (I1)
unnamed: IC68.1 (I0), IC68.13 (I1), IC69.6 (O)
unnamed: IC69.3 (O), IC69.4 (I0), IC69.5 (I1)
PP0_0: IC68.8 (O); also elsewhere on the board
PP1_0: IC70.8 (O); also elsewhere on the board
PP2_0: IC71.8 (O); also elsewhere on the board
PP3_0: IC73.8 (O); also elsewhere on the board
S1: IC69.13 (I1); also elsewhere on the board
S2: IC72.5 (I1); also elsewhere on the board
S3: IC72.10 (I1); also elsewhere on the board
VCC: IC68.14 (VCC), IC69.14 (VCC), IC70.14 (VCC), IC71.14 (VCC), IC72.14 (VCC), IC73.14 (VCC); also elsewhere on the board

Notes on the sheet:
Booth Select 0, 0
Booth Select 1, 0
Booth Select 2, 0
Booth Select 3, 0

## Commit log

2017-02-23 :confetti_ball: Added .gitattributes & .gitignore files
2017-02-23 Initial commit
    Has PFA and CLA schematics
2017-02-26 Added a bunch of new verilog files and a modelsim workspace
2017-03-05 Added eagle project and booth encoder
2017-03-12 Multiplier circuit
2017-05-02 SystemVerilog with assigns
2017-05-30 Functional compare, no memory system
2017-05-30 arithmetic shifter with right rotation
2017-05-31 Functioning rotate
2017-07-25 Added comments and removed old memory structure.
2017-07-30 Memory system rework and python script to convert schematic to verilog
2017-07-31 functioning memory system (minus address bus line), conversion of some muxes to buffer/bus arrangement. Fixed python script module generation.
2017-08-06 Update to memory chip select
2017-08-11 Absolute jump working, memory system partial
    Memory system needs to be able to load and store during PROM op control
2017-09-01 Major updates to schematic. Almost complete except for load/store and non-7004 series.
